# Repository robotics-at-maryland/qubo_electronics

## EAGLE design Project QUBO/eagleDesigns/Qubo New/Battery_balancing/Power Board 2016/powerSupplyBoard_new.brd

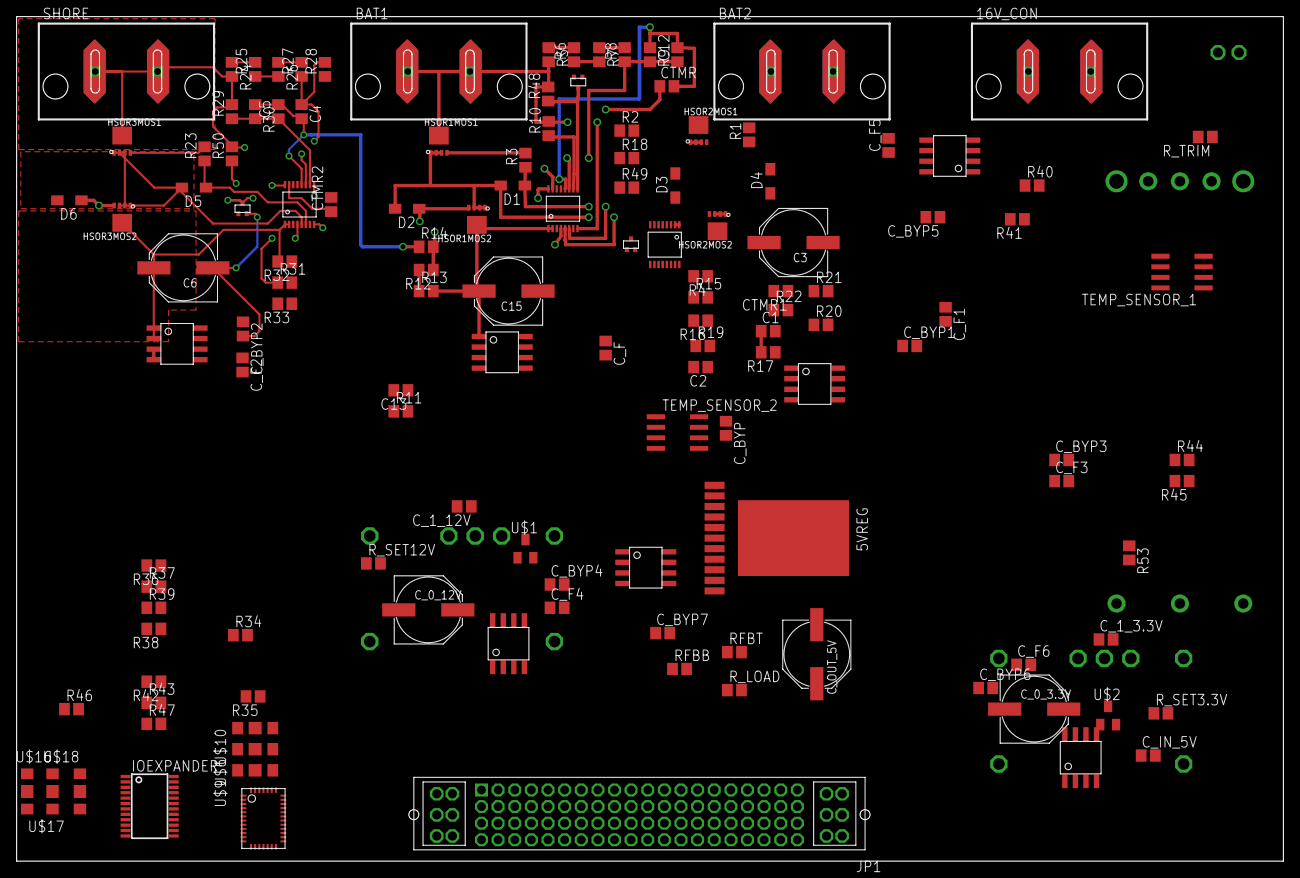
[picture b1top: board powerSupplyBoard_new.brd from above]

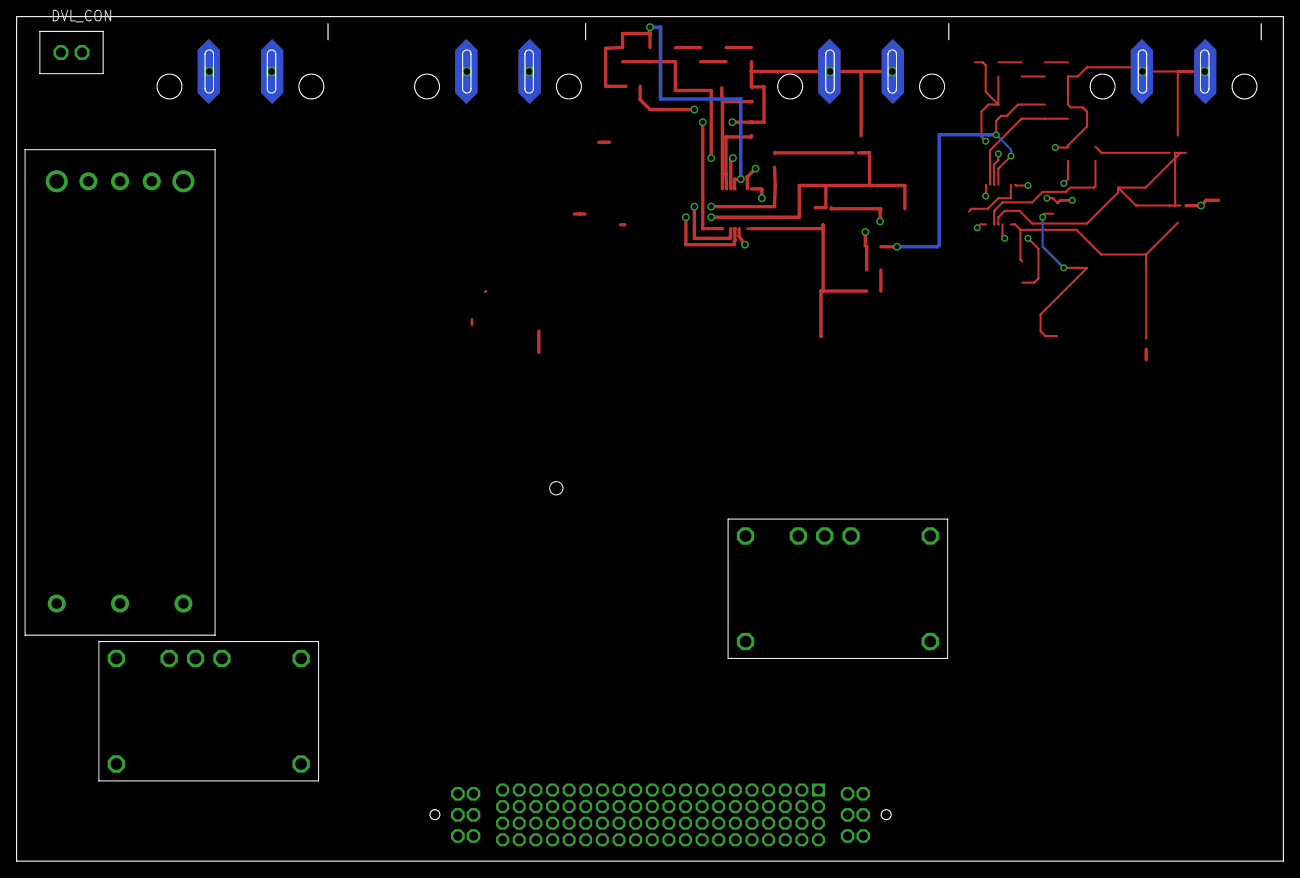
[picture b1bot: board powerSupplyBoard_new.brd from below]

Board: 4 copper layers, 152.4 x 101.6 mm, 137 parts (4 on the bottom side), 105 nets.

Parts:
3.3VCS, 5VCS, 12VCS, 16VCS: ACS713SOIC; ACS713-SOIC
3.3VREG, 12VREG: PTN78060W
5VREG: LMZ23610
16V_CON: SUPERSABRE_2CIRCUIT
ADC: LTC2497UHF; LTC2497-UHF
BAT1, BAT2: SUPERSABRE_2CIRCUIT
BAT1CS, BAT2CS, BAT3CS: ACS713SOIC; ACS713-SOIC
BAT1HSOR, BAT2HSOR, BAT3HSOR: LTC4364MSOP; MSOP16
C1, C4, C12: 1 nF; C0805
C2, C5, C13: 10 nF; C0805
C3, C6, C15: 22 uF; PANASONIC_F
CTMR, CTMR1, CTMR2: 4.7 nF; C0805
C_0_3.3V, C_0_12V: 100 uF; PANASONIC_F
C_1_3.3V, C_1_12V: 2.2 uF; C0805
C_BYP, C_BYP1, C_BYP2, C_BYP3, C_BYP4, C_BYP5, C_BYP6: 0.1 uF; C0805
C_BYP7: .47 uF; C0805
C_F, C_F1, C_F2, C_F3, C_F4, C_F5, C_F6: 47 nF; C0805
C_IN_5V: 10 uF; C0805
C_OUT_5V: 270 uF; PANASONIC_F
D1, D2, D3, D4, D5, D6: SOD323-W
DVL_12VREG: UWEUWE; UWE
DVL_CON: KK254_VERT_2PIN
HIGHSIDEMOS1, HIGHSIDEMOS2, HIGHSIDEMOS3: 2SK3019SOT416/SC75; SOT416
HSOR1MOS1, HSOR1MOS2, HSOR2MOS1, HSOR2MOS2, HSOR3MOS1, HSOR3MOS2: FDMC8360LET40PWR33; POWER33
IOEXPANDER: PCF8575C; PW_R-PDSO-G24
JP1: MPSC-01-80
R1, R3, R23: 10 O; R0805
R2, R5, R24: 2 kO; R0805
R4, R6, R12, R20, R25, R31: 68 kO; R0805
R7, R15, R26, R35, R37, R39, R41, R43, R44, R45, R47, R48, R49, R50, R53: 100 kO; R0805
R8, R16, R27: 820 kO; R0805
R9, R11, R17, R19, R28, R30: 51 kO; R0805
R10, R18, R29: 510 kO; R0805
R13, R21, R32, R42: 430 kO; R0805
R14, R22, R33, R46: 33 kO; R0805
R34, R36, R38, R40: 680 kO; R0805
RFBB: 1.07 kO; R0805
RFBT: 5.62 kO; R0805
R_LOAD: 0.5 O; R0805
R_SET3.3V: 79.3 kO; R0805
R_SET12V: 734 O; R0805
R_TRIM: 15.32 kO; R0805
SHORE: SUPERSABRE_2CIRCUIT
TEMP_SENSOR_1, TEMP_SENSOR_2: LM35
U$1, U$2: BSS138CT-NDSOT23; SOT23
U$6, U$9, U$10, U$16, U$17, U$18: PULLUP_PULLDOWN0805; PULLUP_PULLDOWN_0805

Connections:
3.3CSOUT: 3.3VCS.P$7, ADC.CH6
3.3V: 3.3VCS.P$3, 3.3VCS.P$4, JP1.18, JP1.38, JP1.58, JP1.78, R46.2
3.3VEN: IOEXPANDER.8, U$2.1
5CSOUT: 5VCS.P$7, ADC.CH5
5V: 3.3VCS.P$8, 5VCS.P$3, 5VCS.P$4, 5VCS.P$8, 12VCS.P$8, 16VCS.P$8, ADC.REF+, ADC.VCC, BAT1CS.P$8, BAT2CS.P$8, BAT3CS.P$8, C_BYP.1, C_BYP1.1, C_BYP2.1, C_BYP3.1, C_BYP4.1, C_BYP5.1, C_BYP6.1, IOEXPANDER.24, JP1.17, JP1.37, JP1.57, JP1.77, R44.2, R53.2, TEMP_SENSOR_1.8, TEMP_SENSOR_2.8, U$6.VCC, U$9.VCC, U$10.VCC, U$16.VCC, U$17.GND, U$18.VCC
12CSOUT: 12VCS.P$7, ADC.CH4
12V: 12VCS.P$3, 12VCS.P$4, JP1.16, JP1.36, JP1.56, JP1.76, R42.2
12VEN: IOEXPANDER.7, U$1.1
16CSOUT: 16VCS.P$7, ADC.CH3
16V: 16VCS.P$3, 16VCS.P$4, 16V_CON.P$1, 16V_CON.P$2, JP1.P1,1, JP1.P1,2, JP1.P1,3, JP1.P1,4, JP1.P1,5, JP1.P1,6, R40.2
AGND: 3.3VCS.P$5, 3.3VREG.P$1, 3.3VREG.P$2, 5VCS.P$5, 5VREG.AGND1, 5VREG.AGND2, 5VREG.PGND, 5VREG.SYNC, 12VCS.P$5, 12VREG.P$1, 12VREG.P$2, 16VCS.P$5, ADC.F0, BAT1CS.P$5, BAT1HSOR.GND, BAT2CS.P$5, BAT2HSOR.GND, BAT3CS.P$5, BAT3HSOR.GND, C1.2, C2.2, C3.-, C4.2, C5.2, C6.-, C12.2, C15.-, CTMR.2, CTMR1.2, CTMR2.2, C_0_3.3V.-, C_0_12V.-, C_1_3.3V.2, C_1_12V.2, C_BYP.2, C_BYP1.2, C_BYP2.2, C_BYP3.2, C_BYP4.2, C_BYP5.2, C_BYP6.2, C_BYP7.2, C_F.2, C_F1.2, C_F2.2, C_F3.2, C_F4.2, C_F5.2, C_F6.2, C_IN_5V.2, C_OUT_5V.-, DVL_12VREG.-VIN, HIGHSIDEMOS1.S, HIGHSIDEMOS2.S, HIGHSIDEMOS3.S, JP1.19, JP1.20, JP1.39, JP1.40, JP1.59, JP1.60, JP1.79, JP1.80, R9.1, R14.1, R17.1, R19.1, R22.1, R28.1, R30.1, R33.1, R35.1, R37.1, R39.1, R41.1, R43.1, R45.1, R47.1, RFBB.2, R_LOAD.1, R_SET3.3V.1, R_SET12V.1, TEMP_SENSOR_1.4, TEMP_SENSOR_2.4, U$1.2, U$2.2, U$6.GND, U$9.GND, U$10.GND, U$16.GND, U$17.VCC, U$18.GND
BAT1: BAT1.P$1, BAT1.P$2, BAT1HSOR.VCC, HSOR1MOS1.DRAIN, R5.2, R10.2, R34.2, R48.2
BAT1CSOUT: ADC.CH0, BAT1CS.P$7
BAT1HSOROUT: BAT1CS.P$1, BAT1CS.P$2, BAT1HSOR.OUT, BAT1HSOR.SENSE, C15.+, HSOR1MOS2.DRAIN, R13.2
BAT2: BAT2.P$1, BAT2.P$2, BAT2HSOR.VCC, HSOR2MOS1.DRAIN, R2.2, R18.2, R36.2, R49.2
BAT2CSOUT: ADC.CH1, BAT2CS.P$7
BAT2HSOROUT: BAT2CS.P$1, BAT2CS.P$2, BAT2HSOR.OUT, BAT2HSOR.SENSE, C3.+, HSOR2MOS2.DRAIN, R21.2
BAT3: BAT3HSOR.VCC, HSOR3MOS1.DRAIN, R24.2, R29.2, R38.2, R50.2, SHORE.P$1, SHORE.P$2
BAT3HSOROUT: BAT3CS.P$1, BAT3CS.P$2, BAT3HSOR.OUT, BAT3HSOR.SENSE, C6.+, HSOR3MOS2.DRAIN, R32.2
DGND: ADC.COM, ADC.GND0, ADC.GND1, ADC.GND2, ADC.GND3, ADC.GND4, ADC.GND5, ADC.GND6, ADC.REF-, IOEXPANDER.12, JP1.1, JP1.15, JP1.21, JP1.25, JP1.32, JP1.35, JP1.47, JP1.55, JP1.63, JP1.75, JP1.P2,1, JP1.P2,2, JP1.P2,3, JP1.P2,4, JP1.P2,5, JP1.P2,6
INT_SCL: ADC.SCL, IOEXPANDER.22, JP1.66
INT_SDA: ADC.SDA, IOEXPANDER.23, JP1.65
unnamed: BAT2HSOR.HGATE, D3.C, R1.1
unnamed: HSOR1MOS1.GATE, R3.2
unnamed: BAT2HSOR.DGATE, D4.C, HSOR2MOS2.GATE
unnamed: R2.1, R4.2
unnamed: BAT1HSOR.HGATE, D1.C, R3.1
unnamed: R5.1, R6.2
unnamed: BAT1HSOR.DGATE, D2.C, HSOR1MOS2.GATE
unnamed: R4.1, R15.2
unnamed: BAT3HSOR.SOURCE, D5.A, D6.A, HSOR3MOS1.SOURCE1, HSOR3MOS1.SOURCE2, HSOR3MOS1.SOURCE3, HSOR3MOS2.SOURCE1, HSOR3MOS2.SOURCE2, HSOR3MOS2.SOURCE3
unnamed: R6.1, R7.2
unnamed: R7.1, R8.2
unnamed: BAT1HSOR.OV, C12.1, R8.1, R9.2
unnamed: BAT1HSOR.UV, C13.1, R10.1, R11.2
unnamed: R12.2, R13.1
unnamed: BAT1HSOR.FB, R12.1, R14.2
unnamed: R15.1, R16.2
unnamed: BAT2HSOR.OV, C1.1, R16.1, R17.2
unnamed: BAT1HSOR.TMR, CTMR.1
unnamed: BAT2HSOR.UV, C2.1, R18.1, R19.2
unnamed: R20.2, R21.1
unnamed: BAT2HSOR.FB, R20.1, R22.2
unnamed: C13.2, R11.1
unnamed: BAT1CS.P$6, C_F.1
unnamed: BAT2HSOR.TMR, CTMR1.1
unnamed: BAT2HSOR.SOURCE, D3.A, D4.A, HSOR2MOS1.SOURCE1, HSOR2MOS1.SOURCE2, HSOR2MOS1.SOURCE3, HSOR2MOS2.SOURCE1, HSOR2MOS2.SOURCE2, HSOR2MOS2.SOURCE3
unnamed: HSOR2MOS1.GATE, R1.2
unnamed: BAT2CS.P$6, C_F1.1
unnamed: BAT3HSOR.HGATE, D5.C, R23.1
unnamed: BAT3HSOR.DGATE, D6.C, HSOR3MOS2.GATE
unnamed: ADC.CH7, R34.1, R35.2
unnamed: R24.1, R25.2
unnamed: R25.1, R26.2
unnamed: R26.1, R27.2
unnamed: BAT3HSOR.OV, C4.1, R27.1, R28.2
unnamed: BAT3HSOR.UV, C5.1, R29.1, R30.2
unnamed: R31.2, R32.1
unnamed: BAT1HSOR.SHDN, HIGHSIDEMOS1.D, R48.1
unnamed: BAT3HSOR.FB, R31.1, R33.2
unnamed: BAT3HSOR.TMR, CTMR2.1
unnamed: HSOR3MOS1.GATE, R23.2
unnamed: BAT3CS.P$6, C_F2.1
unnamed: 5VCS.P$1, 5VCS.P$2, 5VREG.VOUT1, 5VREG.VOUT2, C_OUT_5V.+, RFBT.1, R_LOAD.2
unnamed: 5VCS.P$6, C_F3.1
unnamed: 3.3VCS.P$1, 3.3VCS.P$2, 3.3VREG.P$5, 3.3VREG.P$7, C_0_3.3V.+
unnamed: 12VCS.P$6, C_F4.1
unnamed: 12VCS.P$1, 12VCS.P$2, 12VREG.P$5, 12VREG.P$7, C_0_12V.+
unnamed: 16VCS.P$6, C_F5.1
unnamed: DVL_12VREG.+SENSE, DVL_12VREG.+VOUT, DVL_CON.P$1
unnamed: 3.3VCS.P$6, C_F6.1
unnamed: DVL_12VREG.-SENSE, DVL_12VREG.-VOUT, DVL_CON.P$2, R_TRIM.1
unnamed: ADC.CH8, R36.1, R37.2
unnamed: BAT3HSOR.SHDN, HIGHSIDEMOS3.D, R50.1
unnamed: 5VREG.FB, RFBB.1, RFBT.2
unnamed: BAT2HSOR.SHDN, HIGHSIDEMOS2.D, R49.1
unnamed: DVL_12VREG.TRIM, R_TRIM.2
unnamed: ADC.ADCINN, ADC.MUXOUTP
unnamed: ADC.ADCINP, ADC.MUXOUTN
unnamed: ADC.CH9, R38.1, R39.2
unnamed: ADC.CA2, U$10.MID
unnamed: BAT1HSOR.SOURCE, D1.A, D2.A, HSOR1MOS1.SOURCE1, HSOR1MOS1.SOURCE2, HSOR1MOS1.SOURCE3, HSOR1MOS2.SOURCE1, HSOR1MOS2.SOURCE2, HSOR1MOS2.SOURCE3
unnamed: ADC.CA0, U$6.MID
unnamed: ADC.CA1, U$9.MID
unnamed: ADC.CH10, R40.1, R41.2
unnamed: ADC.CH11, R42.1, R43.2
unnamed: ADC.CH12, R44.1, R45.2
unnamed: ADC.CH13, R46.1, R47.2
unnamed: 3.3VREG.P$6, R_SET3.3V.2
unnamed: 12VREG.P$3, U$1.3
unnamed: IOEXPANDER.21, U$17.MID
unnamed: 3.3VREG.P$3, U$2.3
unnamed: 12VREG.P$6, R_SET12V.2
unnamed: 5VREG.SS, C_BYP7.1
unnamed: IOEXPANDER.1, R53.1
unnamed: IOEXPANDER.2, U$16.MID
unnamed: IOEXPANDER.3, U$18.MID
OR1EN: HIGHSIDEMOS1.G, IOEXPANDER.4
OR2EN: HIGHSIDEMOS2.G, IOEXPANDER.5
OR3EN: HIGHSIDEMOS3.G, IOEXPANDER.6
SHORECSOUT: ADC.CH2, BAT3CS.P$7
TEMP1: ADC.CH14, TEMP_SENSOR_1.1
TEMP2: ADC.CH15, TEMP_SENSOR_2.1
UWEEN: DVL_12VREG.ONOFF, IOEXPANDER.9
VIN: 3.3VREG.P$4, 5VREG.VIN1, 5VREG.VIN2, 12VREG.P$4, 16VCS.P$1, 16VCS.P$2, BAT1CS.P$3, BAT1CS.P$4, BAT2CS.P$3, BAT2CS.P$4, BAT3CS.P$3, BAT3CS.P$4, C_1_3.3V.1, C_1_12V.1, C_IN_5V.1, DVL_12VREG.+VIN

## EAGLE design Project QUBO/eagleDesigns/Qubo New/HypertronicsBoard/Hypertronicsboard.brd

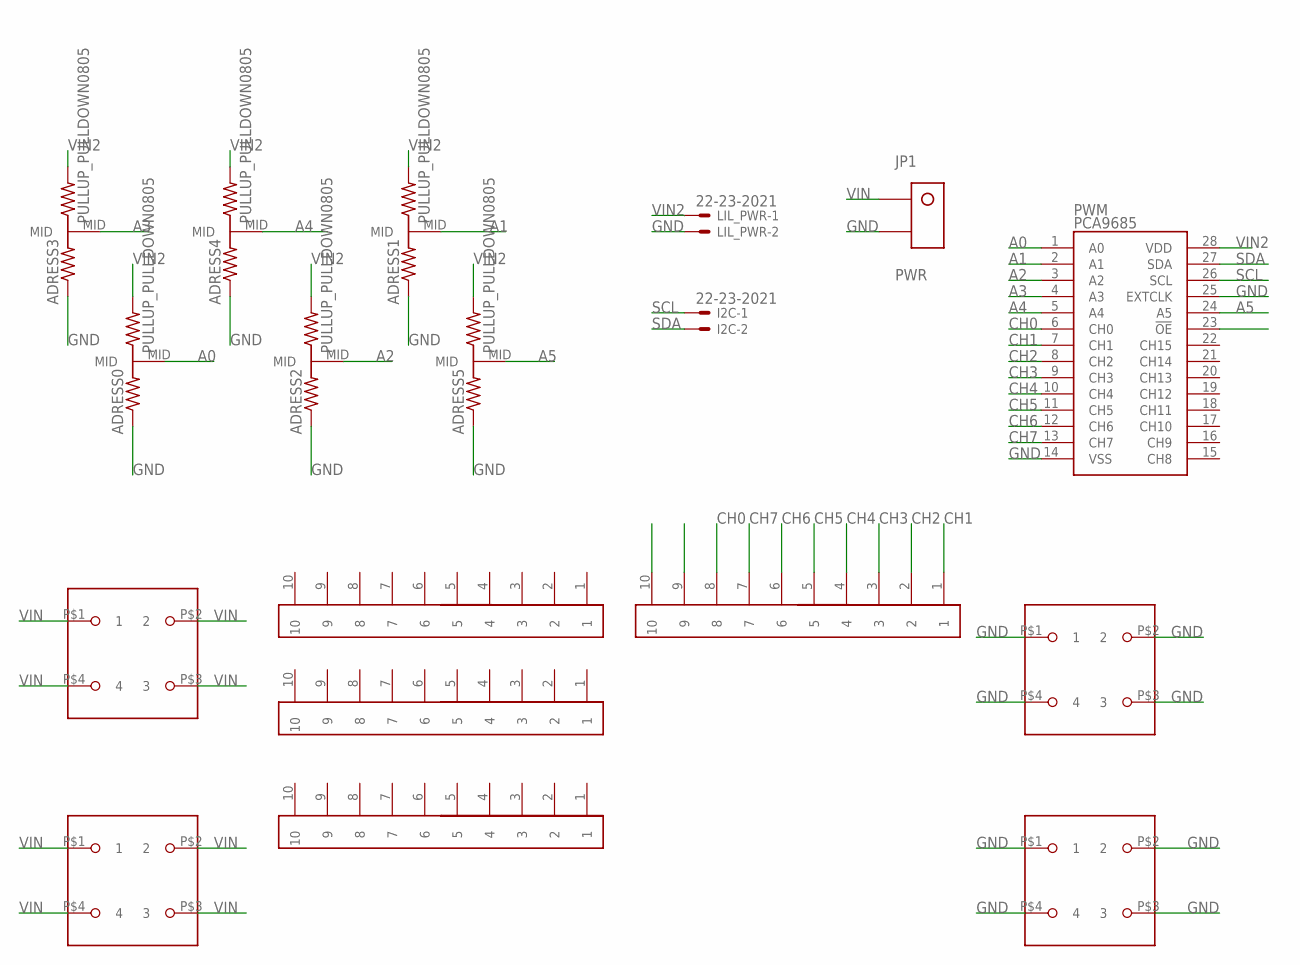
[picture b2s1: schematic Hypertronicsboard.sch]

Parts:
ADRESS0, ADRESS1, ADRESS2, ADRESS3, ADRESS4, ADRESS5: PULLUP_PULLDOWN0805; PULLUP_PULLDOWN_0805
I2C: 22-23-2021
JP1: PWR; SUPERSABRE_2CIRCUIT
LIL_PWR: 22-23-2021
PWM: PCA9685; TSSOP-28_4MM
U$1, U$2, U$3, U$4: BCS-106-L-D-PE-BE; 4-PIN-BIGPOWER
U$5, U$6, U$7, U$10: CONN-RECEPT-2MM-VERT-AU-10POS; 10-PIN-LILPWR

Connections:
A0: ADRESS0.MID, PWM.1 (A0)
A1: ADRESS1.MID, PWM.2 (A1)
A2: ADRESS2.MID, PWM.3 (A2)
A3: ADRESS3.MID, PWM.4 (A3)
A4: ADRESS4.MID, PWM.5 (A4)
A5: ADRESS5.MID, PWM.24 (A5)
CH0: PWM.6 (CH0), U$10.8
CH1: PWM.7 (CH1), U$10.1
CH2: PWM.8 (CH2), U$10.2
CH3: PWM.9 (CH3), U$10.3
CH4: PWM.10 (CH4), U$10.4
CH5: PWM.11 (CH5), U$10.5
CH6: PWM.12 (CH6), U$10.6
CH7: PWM.13 (CH7), U$10.7
GND: ADRESS0.GND, ADRESS1.GND, ADRESS2.GND, ADRESS3.GND, ADRESS4.GND, ADRESS5.GND, JP1.P$2, LIL_PWR.2, PWM.14 (VSS), PWM.25 (EXTCLK), U$3.P$1 (1), U$3.P$2 (2), U$3.P$3 (3), U$3.P$4 (4), U$4.P$1 (1), U$4.P$2 (2), U$4.P$3 (3), U$4.P$4 (4)
SCL: I2C.1, PWM.26 (SCL)
SDA: I2C.2, PWM.27 (SDA)
VIN: JP1.P$1, U$1.P$1 (1), U$1.P$2 (2), U$1.P$3 (3), U$1.P$4 (4), U$2.P$1 (1), U$2.P$2 (2), U$2.P$3 (3), U$2.P$4 (4)
VIN2: ADRESS0.VCC (PWR), ADRESS1.VCC (PWR), ADRESS2.VCC (PWR), ADRESS3.VCC (PWR), ADRESS4.VCC (PWR), ADRESS5.VCC (PWR), LIL_PWR.1, PWM.28 (VDD)

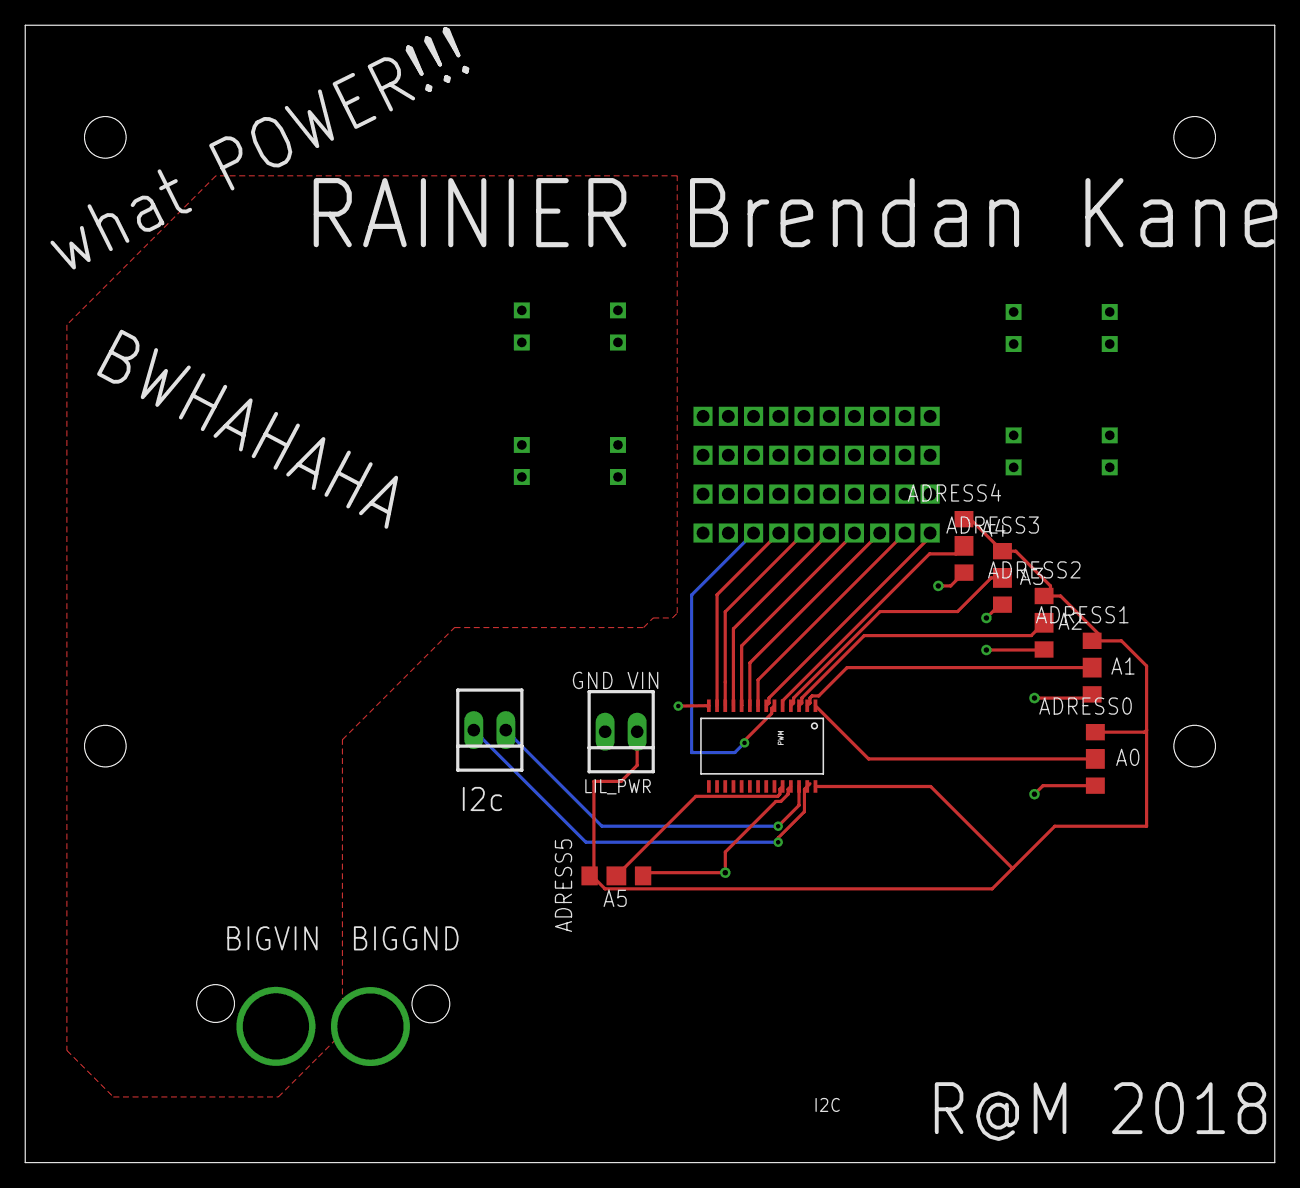
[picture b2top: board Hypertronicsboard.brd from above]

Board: 2 copper layers, 99.1 x 90.2 mm, 18 parts (1 on the bottom side), 19 nets.

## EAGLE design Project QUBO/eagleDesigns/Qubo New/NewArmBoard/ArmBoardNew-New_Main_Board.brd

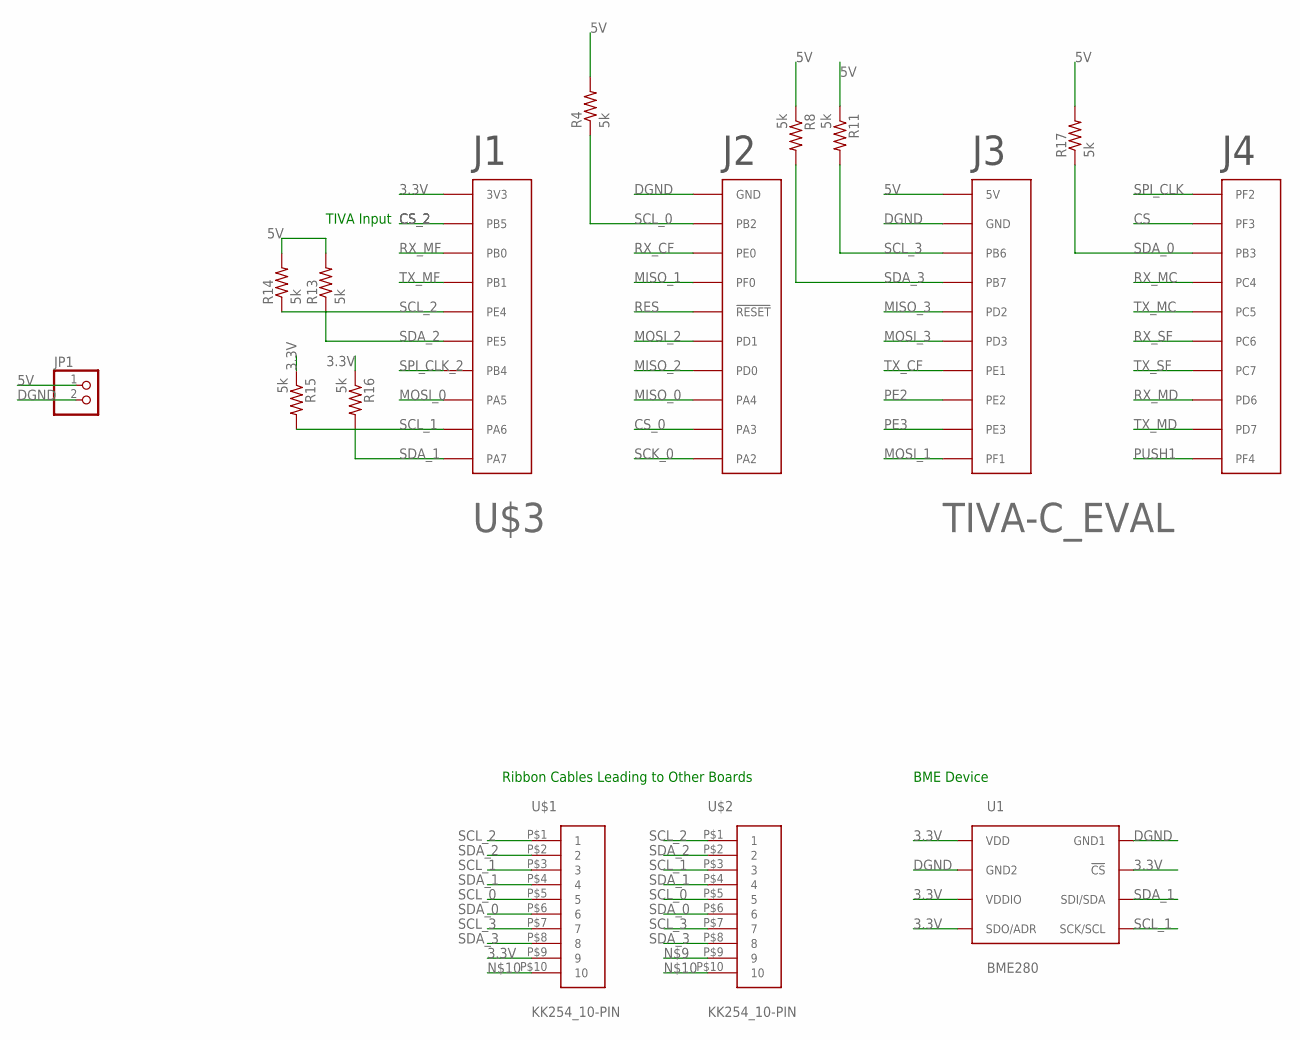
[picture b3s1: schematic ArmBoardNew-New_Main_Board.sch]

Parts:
JP1: PINHD-1X2; 1X02
R4, R8, R11, R13, R14, R15, R16, R17: 5k; R0805
U1: BME280; BME280_LGA
U$1, U$2: KK254_10-PIN
U$3: TIVA-C_EVAL

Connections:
3.3V: R15.1, R16.1, U1.P$2 (!CS), U1.P$5 (SDO/ADR), U1.P$6 (VDDIO), U1.P$8 (VDD), U$1.P$9 (9), U$3.1-1 (3V3)
5V: JP1.1, R4.2, R8.1, R11.1, R13.2, R14.2, R17.2, U$3.3-1 (5V)
CS: U$3.4-2 (PF3)
CS_0: U$3.2-9 (PA3)
CS_2: U$3.1-2 (PB5)
DGND: JP1.2, U1.P$1 (GND1), U1.P$7 (GND2), U$3.2-1 (GND), U$3.3-2 (GND)
MISO_0: U$3.2-8 (PA4)
MISO_1: U$3.2-4 (PF0)
MISO_2: U$3.2-7 (PD0)
MISO_3: U$3.3-5 (PD2)
MOSI_0: U$3.1-8 (PA5)
MOSI_1: U$3.3-10 (PF1)
MOSI_2: U$3.2-6 (PD1)
MOSI_3: U$3.3-6 (PD3)
unnamed: U$1.P$10 (10), U$2.P$10 (10)
PE2: U$3.3-8 (PE2)
PE3: U$3.3-9 (PE3)
PUSH1: U$3.4-10 (PF4)
RES: U$3.2-5 (!RESET!)
RX_CF: U$3.2-3 (PE0)
RX_MC: U$3.4-4 (PC4)
RX_MD: U$3.4-8 (PD6)
RX_MF: U$3.1-3 (PB0)
RX_SF: U$3.4-6 (PC6)
SCK_0: U$3.2-10 (PA2)
SCL_0: R4.1, U$1.P$5 (5), U$2.P$5 (5), U$3.2-2 (PB2)
SCL_1: R15.2, U1.P$4 (SCK/SCL), U$1.P$3 (3), U$2.P$3 (3), U$3.1-9 (PA6)
SCL_2: R14.1, U$1.P$1 (1), U$2.P$1 (1), U$3.1-5 (PE4)
SCL_3: R11.2, U$1.P$7 (7), U$2.P$7 (7), U$3.3-3 (PB6)
SDA_0: R17.1, U$1.P$6 (6), U$2.P$6 (6), U$3.4-3 (PB3)
SDA_1: R16.2, U1.P$3 (SDI/SDA), U$1.P$4 (4), U$2.P$4 (4), U$3.1-10 (PA7)
SDA_2: R13.1, U$1.P$2 (2), U$2.P$2 (2), U$3.1-6 (PE5)
SDA_3: R8.2, U$1.P$8 (8), U$2.P$8 (8), U$3.3-4 (PB7)
SPI_CLK: U$3.4-1 (PF2)
SPI_CLK_2: U$3.1-7 (PB4)
TX_CF: U$3.3-7 (PE1)
TX_MC: U$3.4-5 (PC5)
TX_MD: U$3.4-9 (PD7)
TX_MF: U$3.1-4 (PB1)
TX_SF: U$3.4-7 (PC7)

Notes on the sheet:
Ribbon Cables Leading to Other Boards
BME Device
TIVA Input

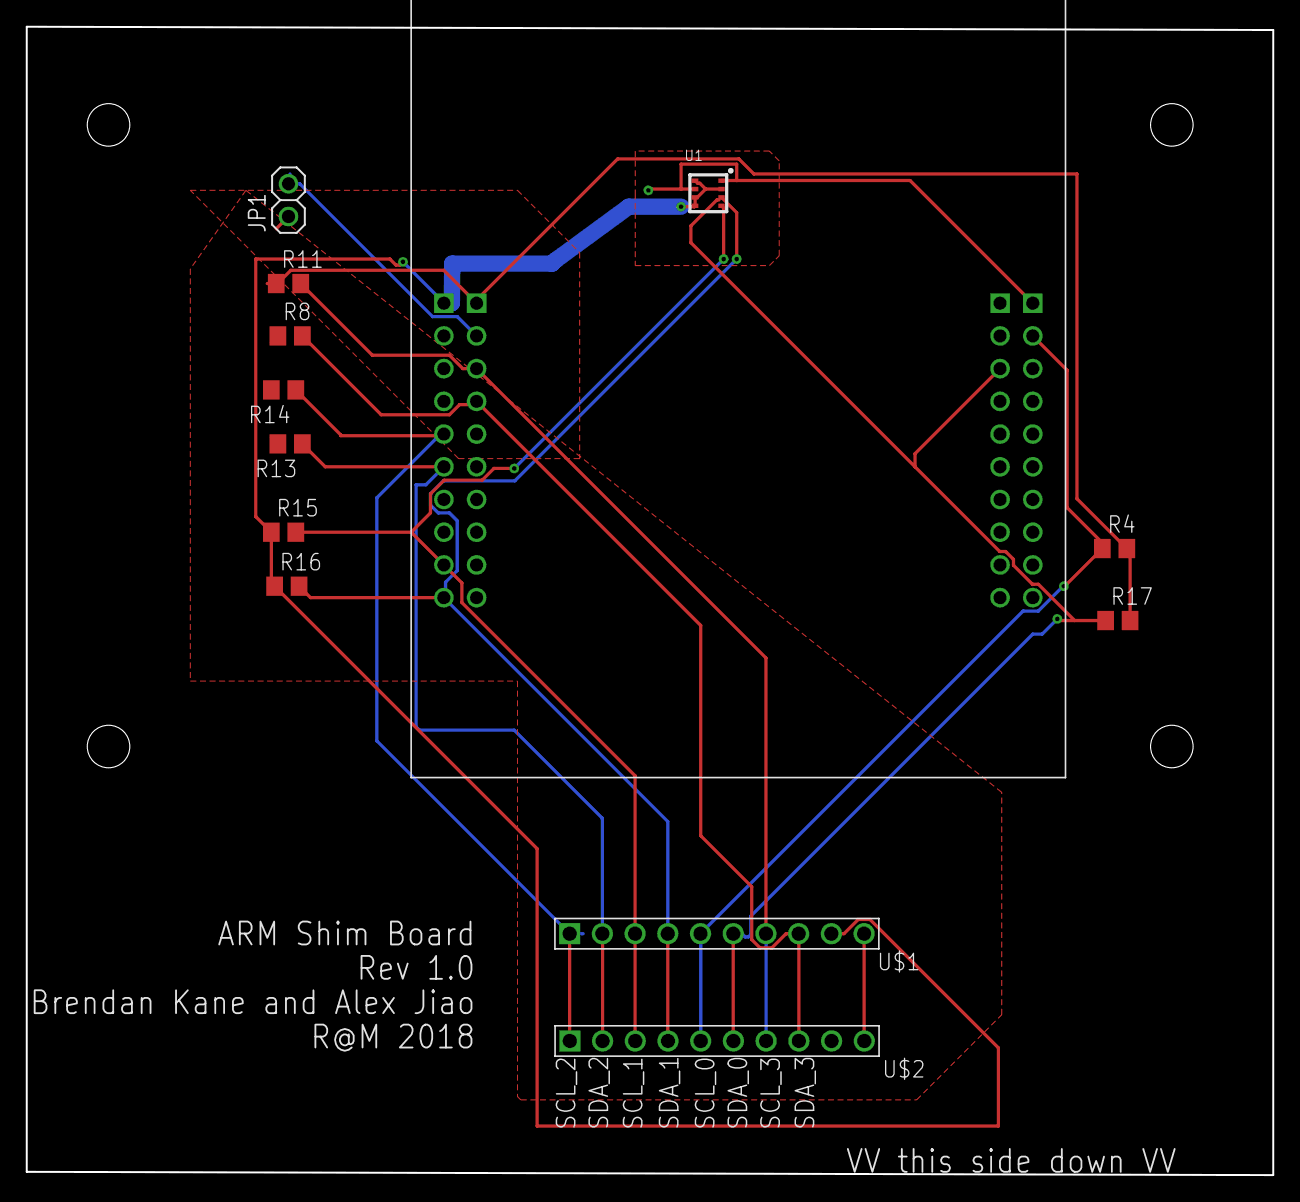
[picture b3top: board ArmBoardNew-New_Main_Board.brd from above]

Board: 2 copper layers, 96.8 x 89.2 mm, 13 parts (0 on the bottom side), 12 nets.

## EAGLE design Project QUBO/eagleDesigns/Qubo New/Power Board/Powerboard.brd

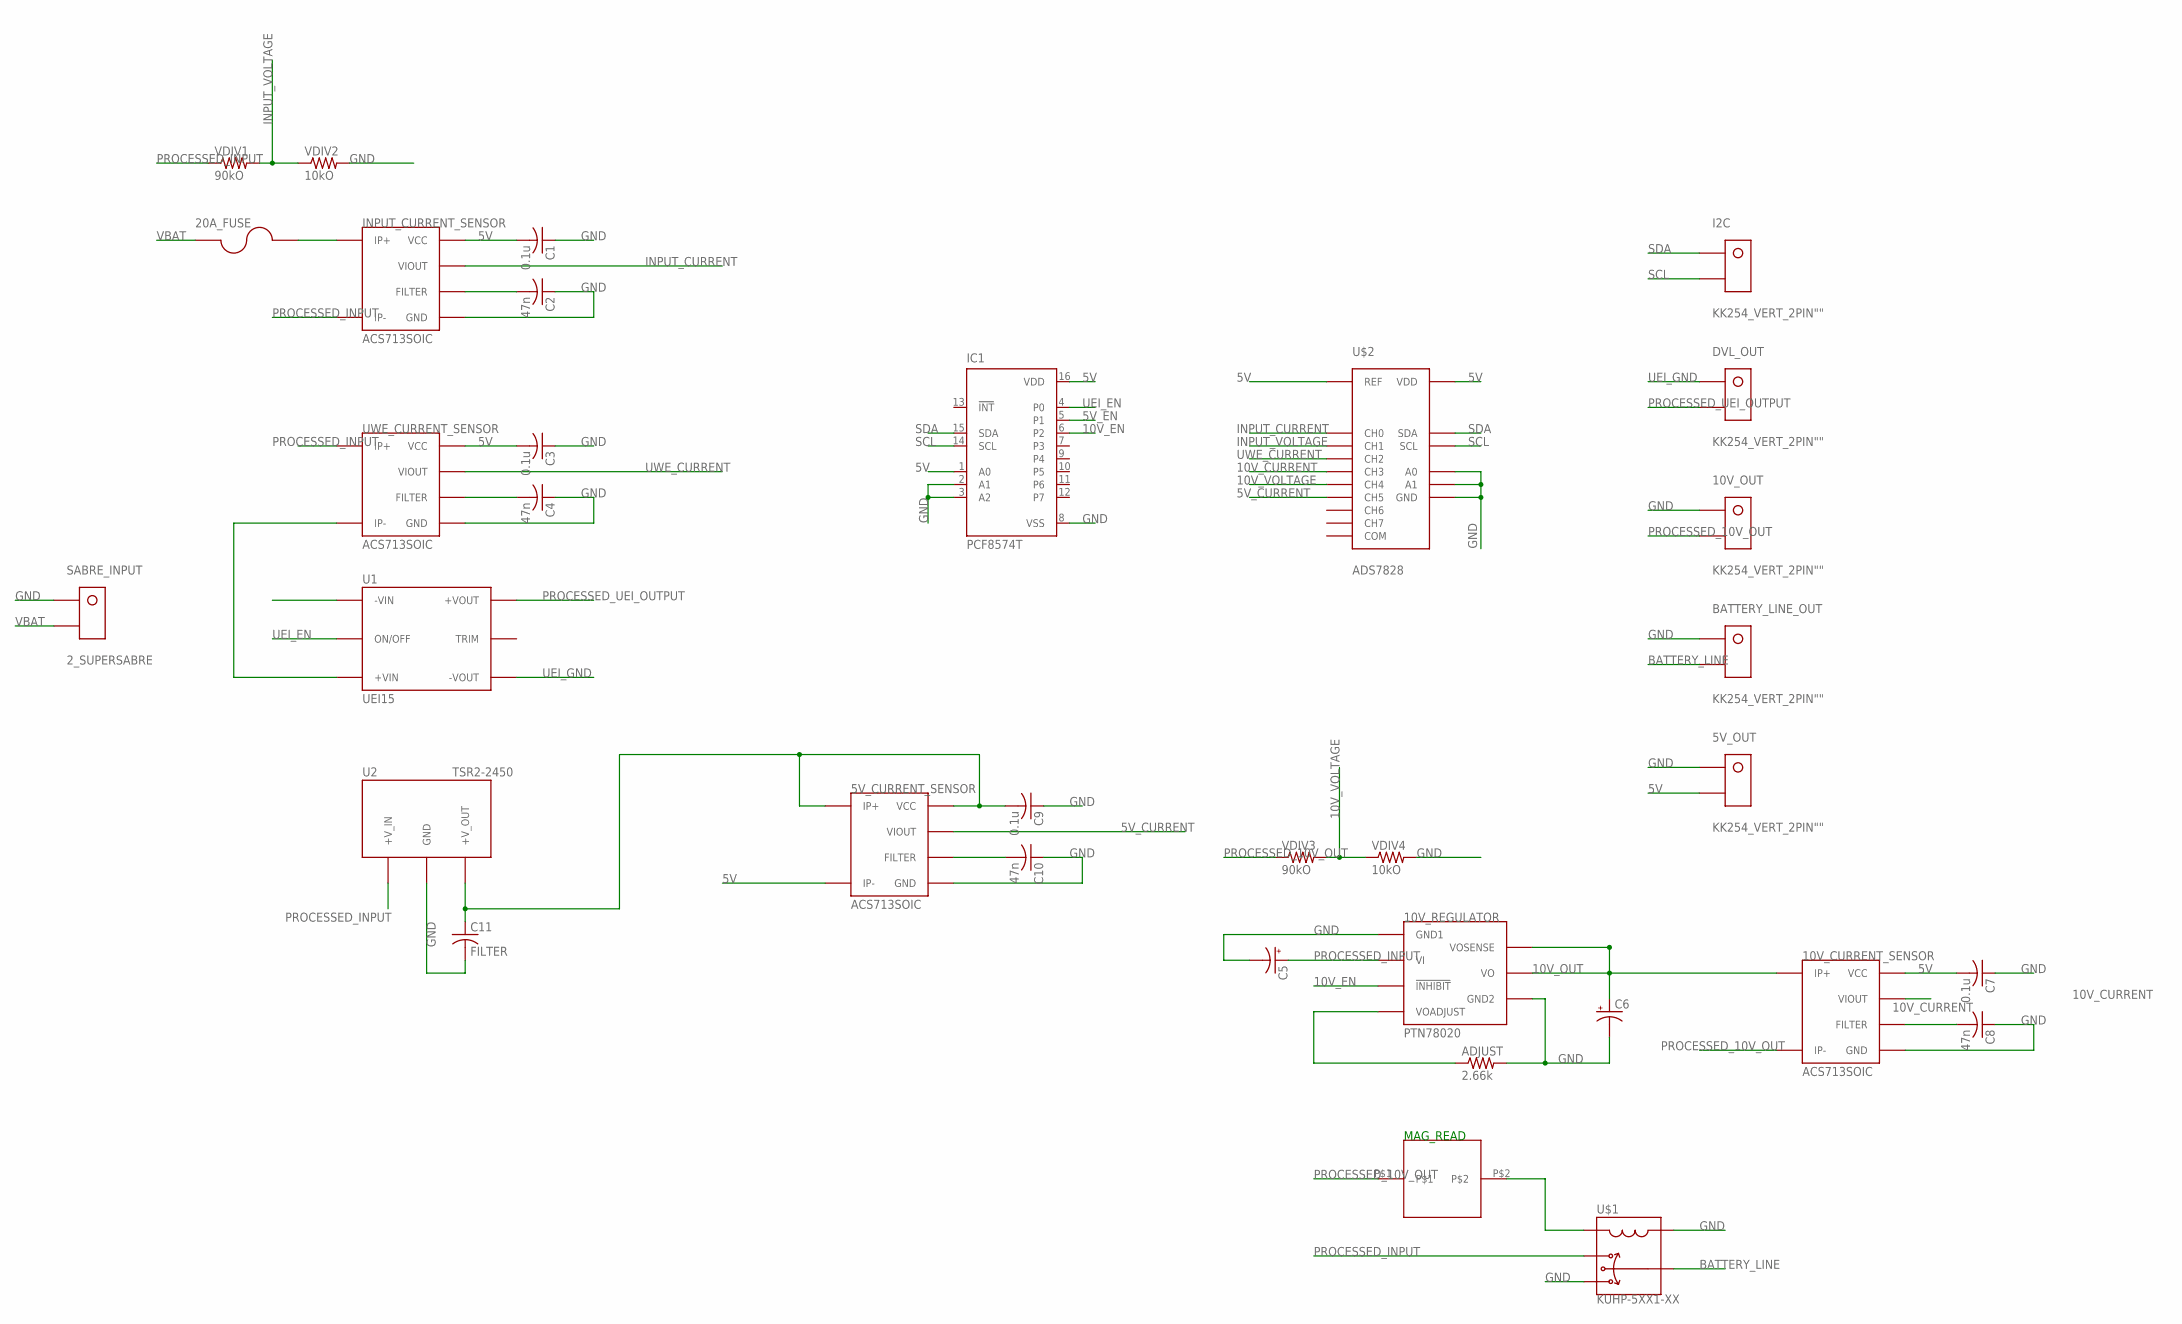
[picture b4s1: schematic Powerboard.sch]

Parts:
5V_CURRENT_SENSOR, 10V_CURRENT_SENSOR: ACS713SOIC; ACS713-SOIC
5V_OUT, 10V_OUT: KK254_VERT_2PIN""; KK254_VERT_2PIN
10V_REGULATOR: PTN78020; PTN
20A_FUSE: BOWED-1.25"-FUSECLIPS; 1.25"_FUSECLIPS
ADJUST: 2.66k; R0805
BATTERY_LINE_OUT: KK254_VERT_2PIN""; KK254_VERT_2PIN
C1, C3, C7, C9: 0.1u; C0805
C2, C4, C8, C10: 47n; C0805
C5, C6: CPOL-US; PANASONIC_A_TYPE_M
C11: FILTER; C0805
DVL_OUT: KK254_VERT_2PIN""; KK254_VERT_2PIN
I2C: KK254_VERT_2PIN""; KK254_VERT_2PIN
IC1: PCF8574T; SO16W
INPUT_CURRENT_SENSOR: ACS713SOIC; ACS713-SOIC
MAGREAD: HE151TR-ND
SABRE_INPUT: 2_SUPERSABRE; SUPERSABRE_2CIRCUIT
U1: UEI15
U2: TSR2-2450; TSR2
U$1: KUHP-5XX1-XX; KUHP_6.35MM-QUICK-CONNECT
U$2: ADS7828; TSSOP16
UWE_CURRENT_SENSOR: ACS713SOIC; ACS713-SOIC
VDIV1, VDIV3: 90kO; R0805
VDIV2, VDIV4: 10kO; R0805

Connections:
5V: 5V_CURRENT_SENSOR.P$3 (IP-), 5V_CURRENT_SENSOR.P$4 (IP-), 5V_OUT.P$2, 10V_CURRENT_SENSOR.P$8 (VCC), C1.2, C3.2, C7.2, IC1.1 (A0), IC1.16 (VDD), INPUT_CURRENT_SENSOR.P$8 (VCC), U$2.10 (REF), U$2.16 (VDD), UWE_CURRENT_SENSOR.P$8 (VCC)
5V_CURRENT: 5V_CURRENT_SENSOR.P$7 (VIOUT), U$2.6 (CH5)
10V_CURRENT: 10V_CURRENT_SENSOR.P$7 (VIOUT), U$2.4 (CH3)
10V_EN: 10V_REGULATOR.INHIBIT (!INHIBIT!), IC1.6 (P2)
10V_OUT: 10V_CURRENT_SENSOR.P$1 (IP+), 10V_CURRENT_SENSOR.P$2 (IP+), 10V_REGULATOR.SENSE (VOSENSE), 10V_REGULATOR.VOUT (VO), C6.+
10V_VOLTAGE: U$2.5 (CH4), VDIV3.2, VDIV4.1
BATTERY_LINE: BATTERY_LINE_OUT.P$2, U$1.7A (7), U$1.7B (7)
GND: 5V_CURRENT_SENSOR.P$5 (GND), 5V_OUT.P$1, 10V_CURRENT_SENSOR.P$5 (GND), 10V_OUT.P$1, 10V_REGULATOR.GND1, 10V_REGULATOR.GND2, ADJUST.2, BATTERY_LINE_OUT.P$1, C1.1, C2.1, C3.1, C4.1, C5.-, C6.-, C7.1, C8.1, C9.1, C10.1, C11.2, IC1.2 (A1), IC1.3 (A2), IC1.8 (VSS), INPUT_CURRENT_SENSOR.P$5 (GND), SABRE_INPUT.P$1, U1.-VIN, U2.2 (GND), U$1.5A (5), U$1.5B (5), U$1.AA (A), U$1.AB (A), U$2.9 (GND), U$2.12 (A0), U$2.13 (A1), UWE_CURRENT_SENSOR.P$5 (GND), VDIV2.2, VDIV4.2
INPUT_CURRENT: INPUT_CURRENT_SENSOR.P$7 (VIOUT), U$2.1 (CH0)
INPUT_VOLTAGE: U$2.2 (CH1), VDIV1.2, VDIV2.1
unnamed: 20A_FUSE.P$3, 20A_FUSE.P$4, INPUT_CURRENT_SENSOR.P$1 (IP+), INPUT_CURRENT_SENSOR.P$2 (IP+)
unnamed: C2.2, INPUT_CURRENT_SENSOR.P$6 (FILTER)
unnamed: 5V_CURRENT_SENSOR.P$6 (FILTER), C10.2
unnamed: 5V_CURRENT_SENSOR.P$1 (IP+), 5V_CURRENT_SENSOR.P$2 (IP+), 5V_CURRENT_SENSOR.P$8 (VCC), C9.2, C11.1, U2.3 (+V_OUT)
unnamed: 10V_REGULATOR.ADJUST (VOADJUST), ADJUST.1
unnamed: U1.+VIN, UWE_CURRENT_SENSOR.P$3 (IP-), UWE_CURRENT_SENSOR.P$4 (IP-)
unnamed: C4.2, UWE_CURRENT_SENSOR.P$6 (FILTER)
unnamed: MAGREAD.P$2, U$1.BA (B), U$1.BB (B)
unnamed: 10V_CURRENT_SENSOR.P$6 (FILTER), C8.2
PROCESSED_10V_OUT: 10V_CURRENT_SENSOR.P$3 (IP-), 10V_CURRENT_SENSOR.P$4 (IP-), 10V_OUT.P$2, MAGREAD.P$1, VDIV3.1
PROCESSED_INPUT: 10V_REGULATOR.VIN (VI), C5.+, INPUT_CURRENT_SENSOR.P$3 (IP-), INPUT_CURRENT_SENSOR.P$4 (IP-), U2.1 (+V_IN), U$1.2A (2), U$1.2B (2), UWE_CURRENT_SENSOR.P$1 (IP+), UWE_CURRENT_SENSOR.P$2 (IP+), VDIV1.1
PROCESSED_UEI_OUTPUT: DVL_OUT.P$2, U1.+VOUT
SCL: I2C.P$2, IC1.14 (SCL), U$2.14 (SCL)
SDA: I2C.P$1, IC1.15 (SDA), U$2.15 (SDA)
UEI_EN: IC1.4 (P0), U1.ON/OFFCNTRL (ON/OFF)
UEI_GND: DVL_OUT.P$1, U1.-VOUT
UWE_CURRENT: U$2.3 (CH2), UWE_CURRENT_SENSOR.P$7 (VIOUT)
VBAT: 20A_FUSE.P$1, 20A_FUSE.P$2, SABRE_INPUT.P$2

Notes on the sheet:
MAG_READ

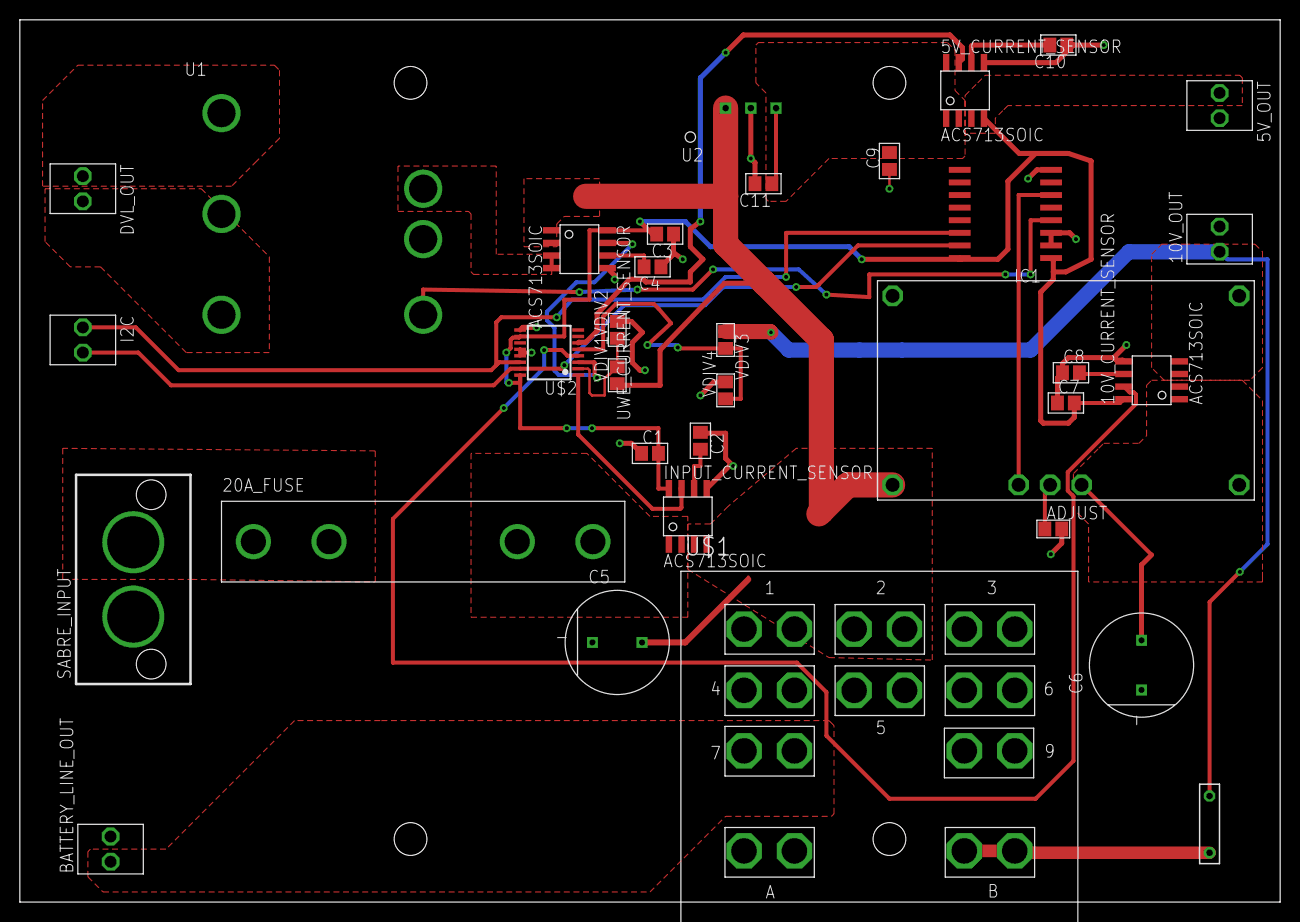
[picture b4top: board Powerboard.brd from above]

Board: 2 copper layers, 127.0 x 88.9 mm, 34 parts (0 on the bottom side), 28 nets.
